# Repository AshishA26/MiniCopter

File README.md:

# MiniCopter
A mini quadcopter that is lightweight (~100g) and designed for agility. It is made using an Arduino Nano, an MPU6050 for orientation sensing, an NRF24L01 for wireless communication, MOSFETs that act as motor drivers, and 8520 motors. The quadcopter is controlled using a custom transmitter that has 2 joysticks and an NRF24L01, and uses PID motor control for stabilizing roll and pitch of the quadcopter. In addition, I created a custom PCB to house all these components and allow for better wiring, testing, and weight reduction.

Programmed in `Arduino IDE`, models created in `Autodesk Inventor`, schematics and PCB created in `KiCad`.

Demo showing the PID motor control of the quadcopter that allows for the quadcopter to stabilize and balance ([full video](https://www.youtube.com/watch?v=k4_8MwJ_Zw4)):

## PCB Design
My original design used a perfboard, but I eventually designed a 2-layer PCB that would not only simplify debugging and wire routing, but also allow for some weight reduction. 

The PCB contains all circuitry and the connections between them. The placement, orientation, and connections of each component was carefully considered when making decisions on the design of the PCB. The size of the PCB itself was also an important factor for me to consider because I needed to be the smallest and most optimal size it could be in order to reduce the weight on the quadcopter.

The PCB also acts as custom motor drivers for each motor by employing the use of MOSFETs, as normal Arduino motor drivers available online are too large and are not meant for high current flow and high speeds. 

Through calculations, I determined the trace size required for each component on the board, such as the LiPo battery connections needing thicker traces due to the high current. After various tests, it was found that dupont connectors could not be used to transfer current to the motors as the end connectors had resistance, so having a PCB with custom trace sizes was very useful.

Additionally, through testing on the Perfboard, I found that 2 LiPo batteries were required as I not only needed to power the 4 motors, but also the Arduino (which also powers other components).

### Routing

### Original Perfboard Design

| Perfboard Front Side | Perfboard Back Side |
| :---: | :---: |
|   |  |
| Back side of complete perfboard | Perfboard on minicoptoper |
|   |  |

## Schematics

## Part Pictures
After many tests and designs, the final chassis has been built such that the frame is strong and firm enough, while greatly reducing weight. The propellor gaurds have also been iteratively designed after numerous tests such that it protects people and the quadcopter, while also being very lightweight.

## Other Tests

Checkout some [flight testing](https://www.youtube.com/watch?v=XLUD_ImCz4A).

Checkout a demo of [the joystick wirelessly controlling a motor](https://www.youtube.com/watch?v=rh6yMr4QYGM).

To determine the strength of each motor, I 3D printed some parts and flipped the motor upside down to conduct a thrust analysis. This allowed me to see if the MOSFETs and batteries would be able to supply enough current to the motors.

## Setup
- To open the schematics and pcb, install my [KiCAD libraries](https://github.com/AbhinavA10/kicad-libraries).

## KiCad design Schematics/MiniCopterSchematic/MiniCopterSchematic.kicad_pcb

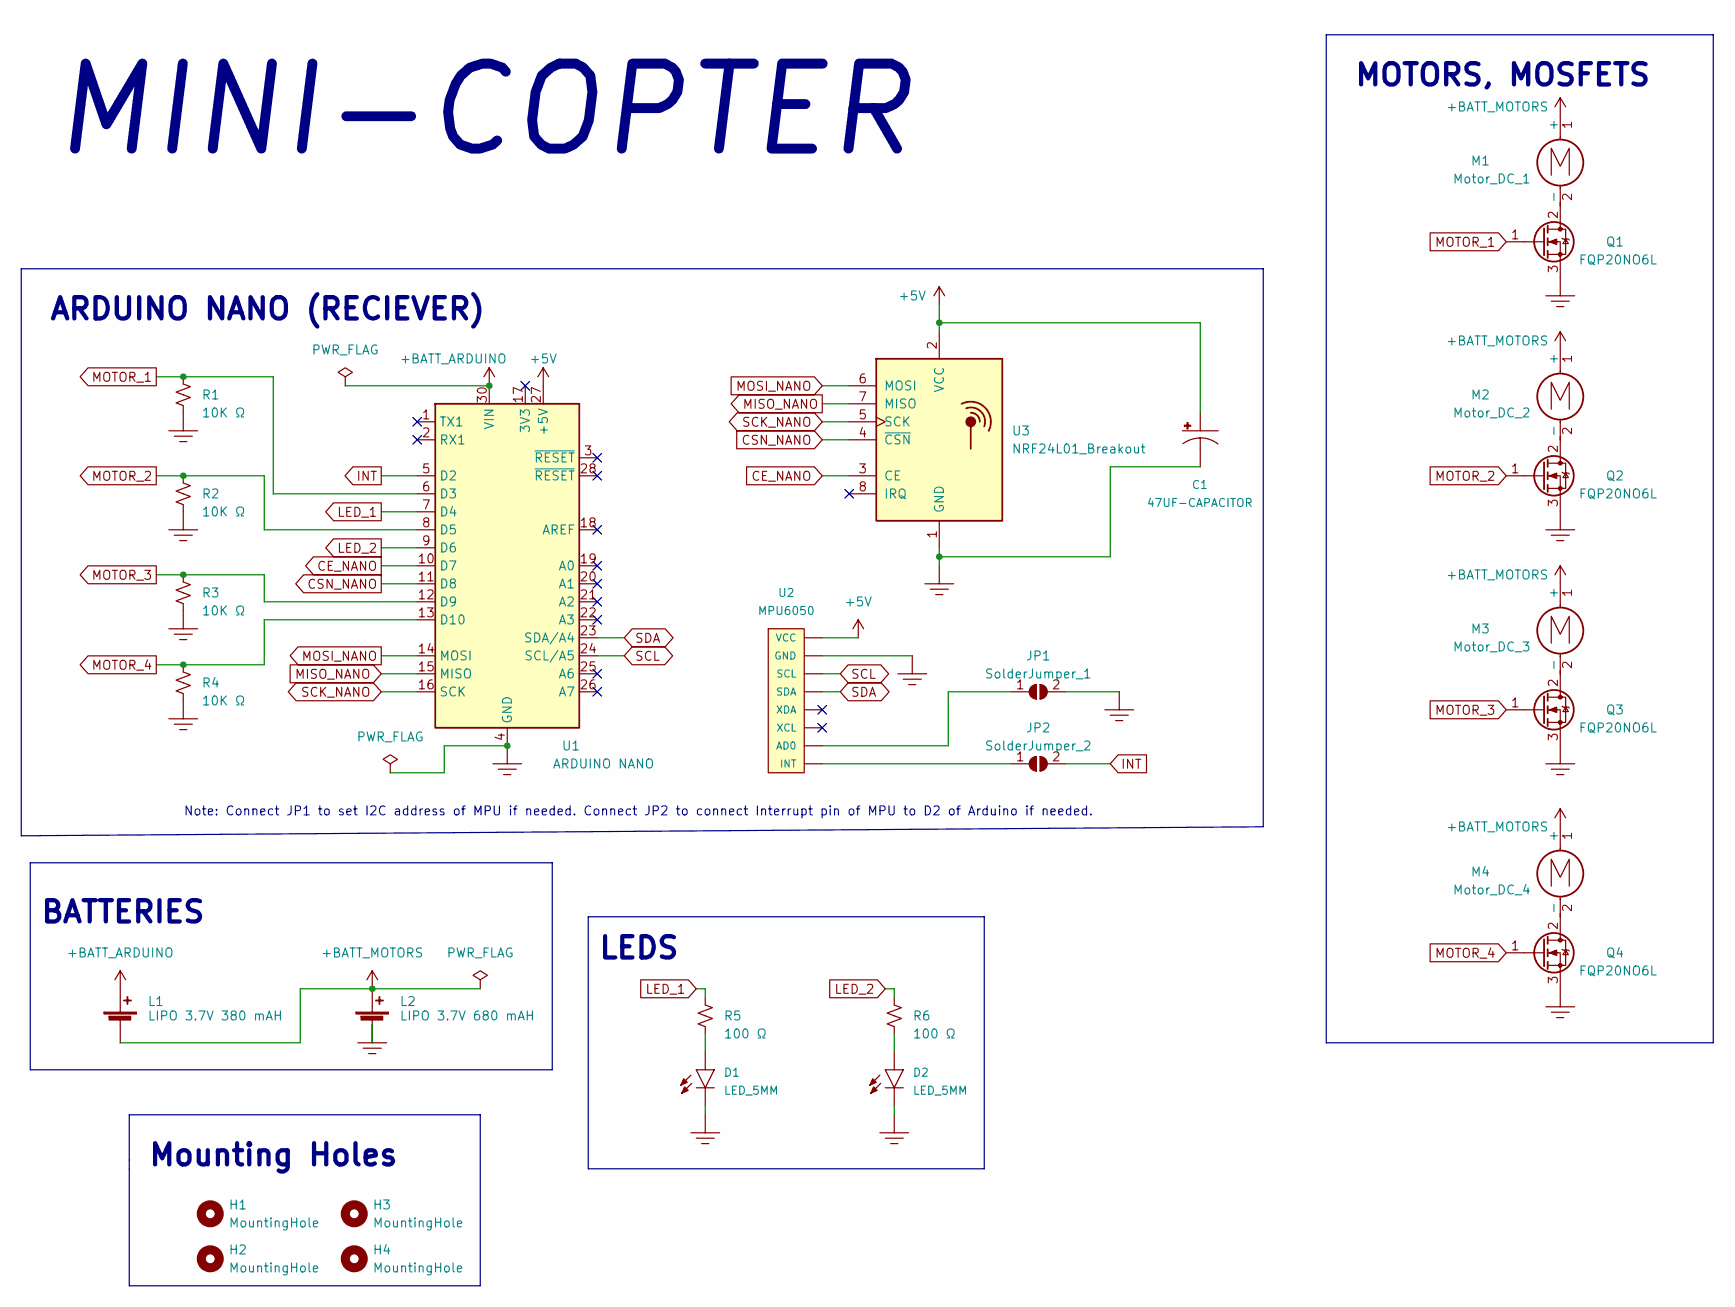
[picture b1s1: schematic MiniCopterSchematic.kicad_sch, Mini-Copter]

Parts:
C1: 47UF-CAPACITOR; CP_Radial_D6.3mm_P2.50mm
D1, D2: LED_5MM; LED_D5.0mm
H1, H2, H3, H4: MountingHole; MountingHole_3.2mm_M3_Pad
JP1: SolderJumper_1; PinHeader_1x02_P2.54mm_Vertical
JP2: SolderJumper_2; PinHeader_1x02_P2.54mm_Vertical
L1: LIPO 3.7V 380 mAH; PowerPad_Pair_5.0x5.0mm
L2: LIPO 3.7V 680 mAH; PowerPad_Pair_5.0x5.0mm_1PadFlipped
M1: Motor_DC_1; PowerPad_Pair_3.0x3.0mm
M2: Motor_DC_2; PowerPad_Pair_3.0x3.0mm
M3: Motor_DC_3; PowerPad_Pair_3.0x3.0mm
M4: Motor_DC_4; PowerPad_Pair_3.0x3.0mm
Q1, Q2, Q3, Q4: FQP20NO6L; 3Pin_MOSFET_MotorDriver
R1, R2, R3, R4: 10K Ω; R_Axial_DIN0207_L6.3mm_D2.5mm_P10.16mm_Horizontal
R5, R6: 100 Ω; R_Axial_DIN0207_L6.3mm_D2.5mm_P10.16mm_Horizontal
U1: ARDUINO NANO; Arduino_Nano
U2: MPU6050
U3: NRF24L01_Breakout

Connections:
+5V: C1.1 (+), U1.27 (+5V), U2.1 (VCC), U3.2 (VCC)
+BATT_ARDUINO: L1.1 (+), U1.30 (VIN)
+BATT_MOTORS: L1.2 (-), L2.1 (+), M1.1 (+), M2.1 (+), M3.1 (+), M4.1 (+)
CE_NANO: U1.10 (D7), U3.3 (CE)
CSN_NANO: U1.11 (D8), U3.4 (~CSN)
GND: C1.2 (-), D1.2, D2.2, JP1.2 (B), L2.2 (-), Q1.3 (S), Q2.3 (S), Q3.3 (S), Q4.3 (S), R1.2, R2.2, R3.2, R4.2, U1.4 (GND), U1.29 (GND), U2.2 (GND), U3.1 (GND)
INT: JP2.2 (B), U1.5 (D2)
LED_1: R5.1, U1.7 (D4)
LED_2: R6.1, U1.9 (D6)
MISO_NANO: U1.15 (MISO), U3.7 (MISO)
MOSI_NANO: U1.14 (MOSI), U3.6 (MOSI)
MOTOR_1: Q1.1 (G), R1.1, U1.6 (D3)
MOTOR_2: Q2.1 (G), R2.1, U1.8 (D5)
MOTOR_3: Q3.1 (G), R3.1, U1.12 (D9)
MOTOR_4: Q4.1 (G), R4.1, U1.13 (D10)
unnamed: D1.1, R5.2
unnamed: D2.1, R6.2
unnamed: JP1.1 (A), U2.7 (AD0)
unnamed: JP2.1 (A), U2.8 (INT)
unnamed: M1.2 (-), Q1.2 (D)
unnamed: M2.2 (-), Q2.2 (D)
unnamed: M3.2 (-), Q3.2 (D)
unnamed: M4.2 (-), Q4.2 (D)
SCK_NANO: U1.16 (SCK), U3.5 (SCK)
SCL: U1.24 (SCL/A5), U2.3 (SCL)
SDA: U1.23 (SDA/A4), U2.4 (SDA)

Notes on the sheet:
ARDUINO NANO (RECIEVER)
Note: Connect JP1 to set I2C address of MPU if needed. Connect JP2 to connect Interrupt pin of MPU to D2 of Arduino if needed.
MINI-COPTER
BATTERIES
LEDS
Mounting Holes
MOTORS, MOSFETS

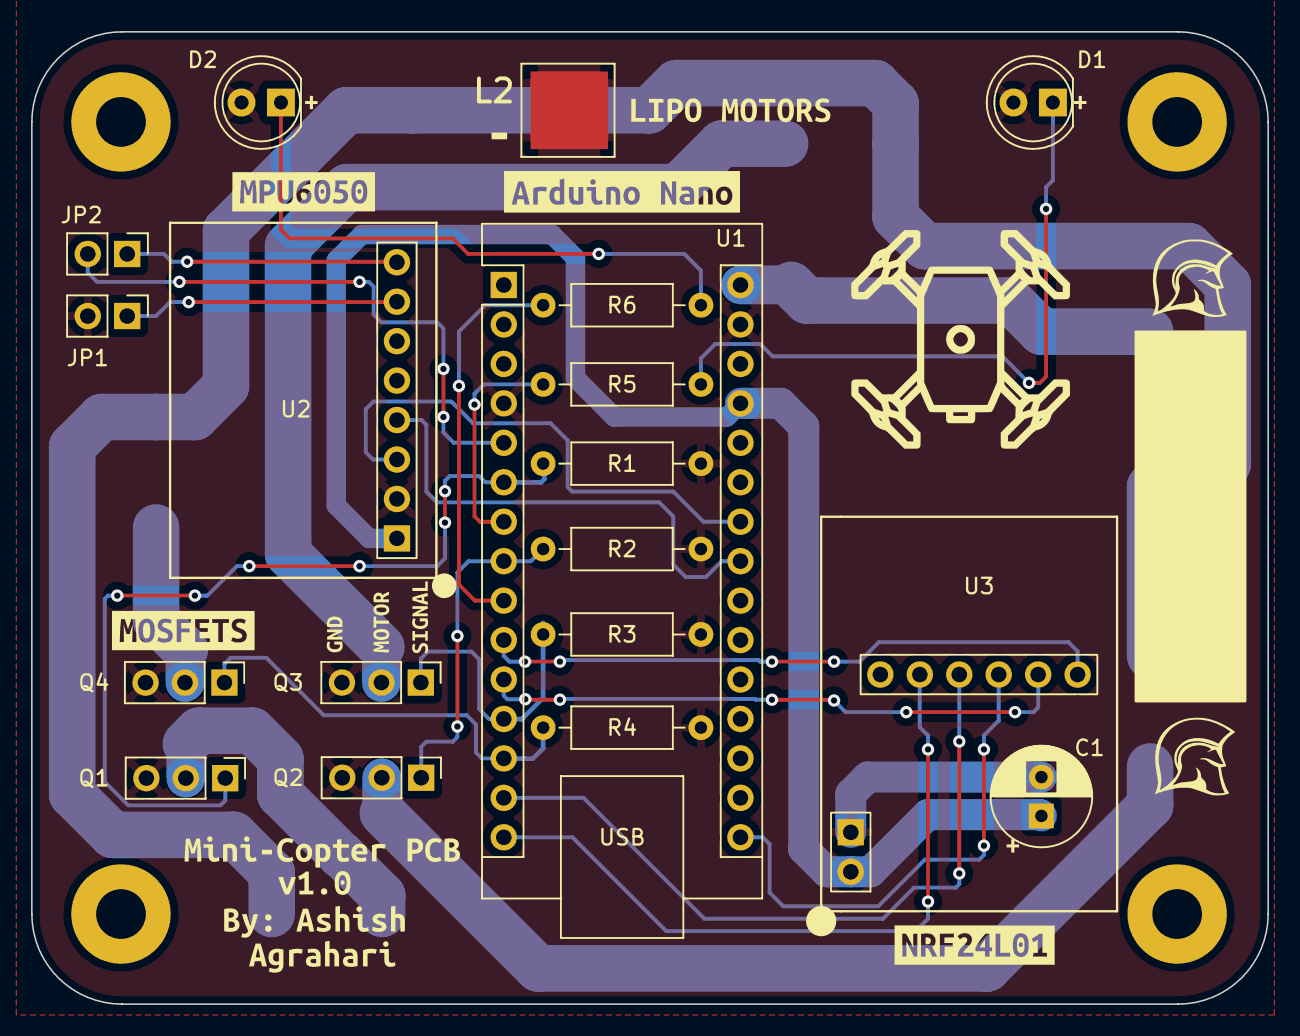
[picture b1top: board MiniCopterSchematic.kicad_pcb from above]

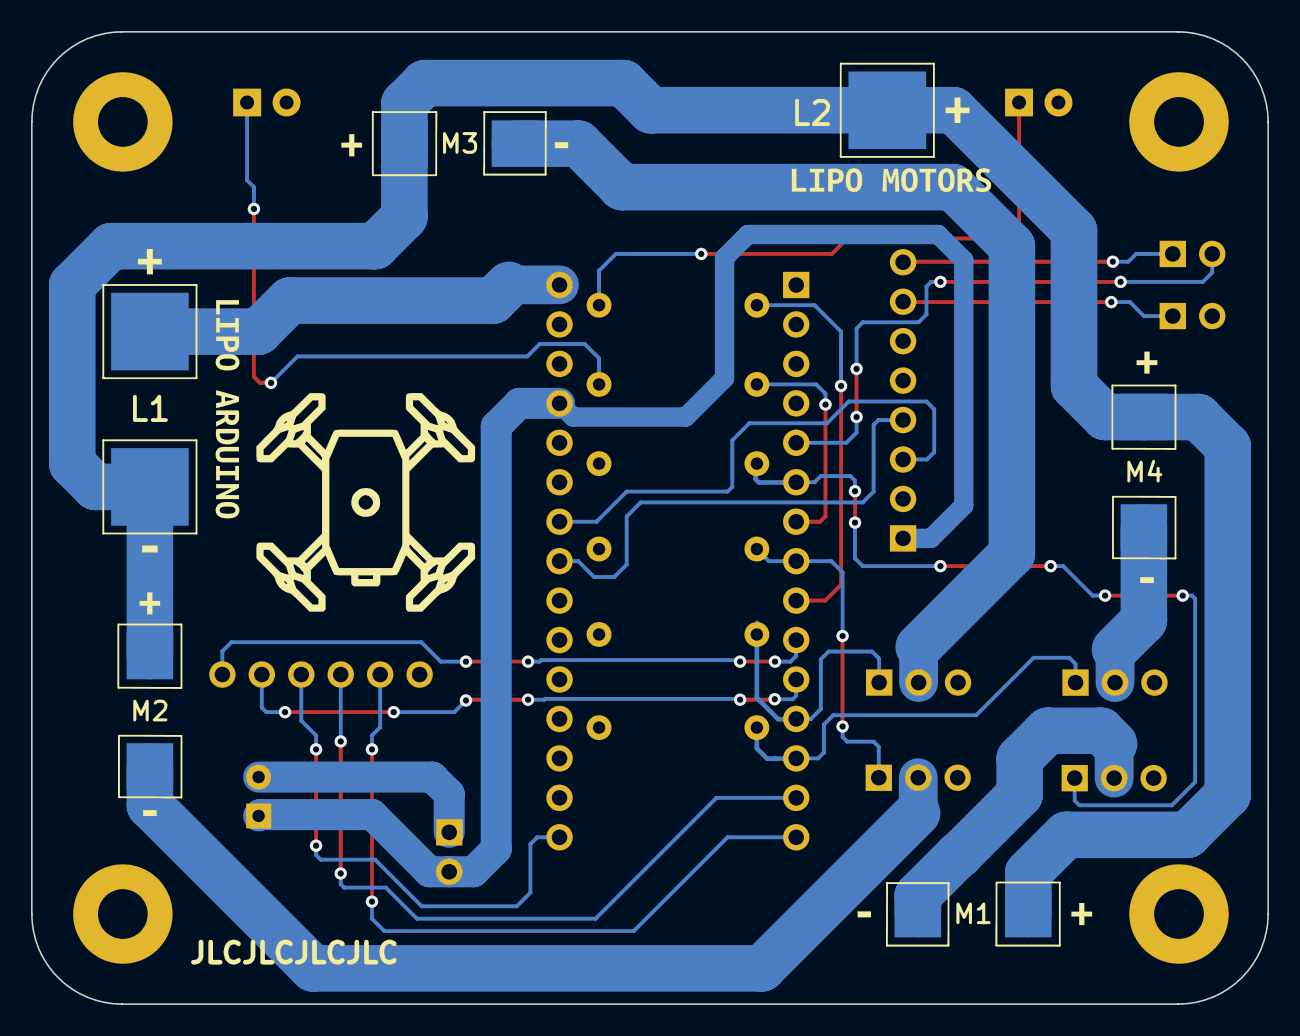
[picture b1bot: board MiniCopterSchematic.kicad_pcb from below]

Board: 2 copper layers, 79.6 x 62.6 mm, 57 parts (9 on the bottom side), 26 nets.

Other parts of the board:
kibuzzard-644F1CFC: G***; kibuzzard-644F1CFC
kibuzzard-644F1D01: G***; kibuzzard-644F1D01
kibuzzard-644F1F4C: G***; kibuzzard-644F1F4C
kibuzzard-644F1F5E: G***; kibuzzard-644F1F5E
kibuzzard-644F1F53: G***; kibuzzard-644F1F53
kibuzzard-644F1F59: G***; kibuzzard-644F1F59
kibuzzard-644F15D5: G***; kibuzzard-644F15D5
kibuzzard-644F152E: G***; kibuzzard-644F152E
kibuzzard-644F167C: G***; kibuzzard-644F167C
kibuzzard-644F1527: G***; kibuzzard-644F1527
kibuzzard-644F2052: G***; kibuzzard-644F2052
kibuzzard-644F2068: G***; kibuzzard-644F2068
kibuzzard-644F2071: G***; kibuzzard-644F2071
kibuzzard-6440B80B, kibuzzard-6440B80B#2, kibuzzard-6440B80B#3, kibuzzard-6440B80B#4: G***; kibuzzard-6440B80B
kibuzzard-6440B803, kibuzzard-6440B803#2, kibuzzard-6440B803#3, kibuzzard-6440B803#4: G***; kibuzzard-6440B803
kibuzzard-6440D5EF: G***; kibuzzard-6440D5EF
kibuzzard-6440D61E: G***; kibuzzard-6440D61E
kibuzzard-6440D635: G***; kibuzzard-6440D635
kibuzzard-6452D829: G***; kibuzzard-6452D829
kibuzzard-6452DC3B: G***; kibuzzard-6452DC3B
kibuzzard-6452DC31: G***; kibuzzard-6452DC31
kibuzzard-6452DC36: G***; kibuzzard-6452DC36
kibuzzard-6452DC40: G***; kibuzzard-6452DC40

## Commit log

2022-12-20 Create Test
2022-12-20 Uploaded MPU test code (teapot demo)
2022-12-20 Deleted a test file
2022-12-20 Created readme with instructions for mpu
2023-01-09 Testing NRF
2023-01-11 Create r
2023-01-11 Uploaded Motor Dimensions
2023-01-19 Added models
2023-01-23 Added joystick to motor code
2023-01-27 Working on schematic
2023-01-27 Updating schematic
2023-01-27 Finished Schematic
2023-01-27 Updated schematic
2023-01-28 Working on organizing perfboard
2023-01-31 Combined MPU and nRF code
2023-02-13 Added libraries
2023-02-13 Added readme
2023-02-13 Fixed bugs
2023-02-14 Fixing files
2023-02-14 Working on chasssis
2023-02-17 Working on 3D model for chassis
2023-02-17 Working on assembly
2023-02-17 Made major modifications to chassis to decrease weight
2023-02-20 Updating libraries
2023-02-22 Made prop guard thinner
2023-02-23 Organizing repo
2023-02-23 Updated schematic, added pictures, updated readme
2023-02-27 Moved schematic to images folder
2023-02-28 Added killswitch to remotely turn on/off the copter
2023-03-01 Reduced weight of propeller gaurd
2023-03-03 Added some notes
2023-03-04 Update photos
2023-03-04 fixed typo
2023-03-06 Added balancing code, working on adjusting values
2023-03-08 Made chassis lighter
2023-03-30 Assigned footprints to symbols
2023-04-03 Testing kp values for PID control
2023-04-06 Working on PCB for copter
2023-04-15 Working on PCB layout/wiring
2023-04-17 Working on PCB
2023-04-20 Fixing layout of components on PCB
2023-04-20 Working on PCB organizing and putting on text
2023-04-20 Fixed a lot of errors in the schematic which had caused PCB issues
2023-04-20 Working on PCB routing
2023-04-21 Organizing schematics
2023-04-23 Working on routing
2023-04-25 Cleaning up board
2023-04-28 Added capacitor, changed track widths on PCB
2023-04-28 Added LEDs
2023-04-29 Making PCB look good
2023-04-29 Updated labels
2023-04-29 Added logos
2023-05-01 PCB design finalizing
2023-05-01 Finalizing PCB
2023-05-01 Fixed mosfet pinouts
2023-05-02 Finalized PCB
2023-05-02 Created gerber files
2023-05-02 Fixed size of pin holes
2023-05-02 Created zip file for gerbers
2023-05-03 Updated PCB traces, added 5mm LEDS
2023-05-04 Made new gerber files
2023-06-09 Updated models for pcb
2023-06-12 Partially Fixed balancing
2023-06-22 Updated schematics and pics
2023-06-25 Organized files
2023-06-25 Moved code files
